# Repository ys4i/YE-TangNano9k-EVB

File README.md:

# YE-TangNano9k-EValuationBoard

コミックマーケット(C106)同人誌用TangNano9kの開発ボードです  
某月電子通商 Bタイプ基板(95×72mm)と寸法に互換性があります  
`販売コード[110243] B基板用アクリルパネル(アクリル板) 2mm厚(透明)`  
などでパネルを作れます

Tang Nano 9Kを用いた評価用ボードです。KiCad 9.0.3で設計されており、コミックマーケット(C106)頒布向けに作成されました。

## 特長
- 基板サイズ: 95 mm × 72 mm。某月電子通商 Bタイプ基板と同寸で、市販のB基板用アクリルパネルが使用可能。
- Seeed Studio製Tang Nano 9Kモジュールを搭載 (U1)。
- 24ピン×2列の拡張用ソケットコネクタを左右に配置 (J1, J2)。
- 4桁7セグメントLED表示器 OSL40391-IRA を搭載し、簡単な数値表示が可能。
- ブザー UGCM1205XP と、駆動用NPNトランジスタ 2SC1815 (Q1) を装備。
- 入力インターフェースとして SPDTスイッチ (SW1) とタクトスイッチ2個 (SW2, SW3) を搭載。

## プロジェクト構成
- `YE-tangnano9k-EVB.kicad_pro` : プロジェクト設定ファイル
- `YE-tangnano9k-EVB.kicad_sch` : 回路図
- `YE-tangnano9k-EVB.kicad_pcb` : 基板レイアウト
- `docs/YE-tangnano9k-EVB.pdf` : 回路図・基板図の閲覧用PDF
- `sym-lib-table` : シンボルライブラリ設定

## 使い方
KiCad 9.0以降で `.kicad_pro` ファイルを開き、回路図や基板データを編集してください。ファイル形式の詳細は [KiCad File Formats Documentation](https://dev-docs.kicad.org/en/file-formats/index.html) を参照してください。

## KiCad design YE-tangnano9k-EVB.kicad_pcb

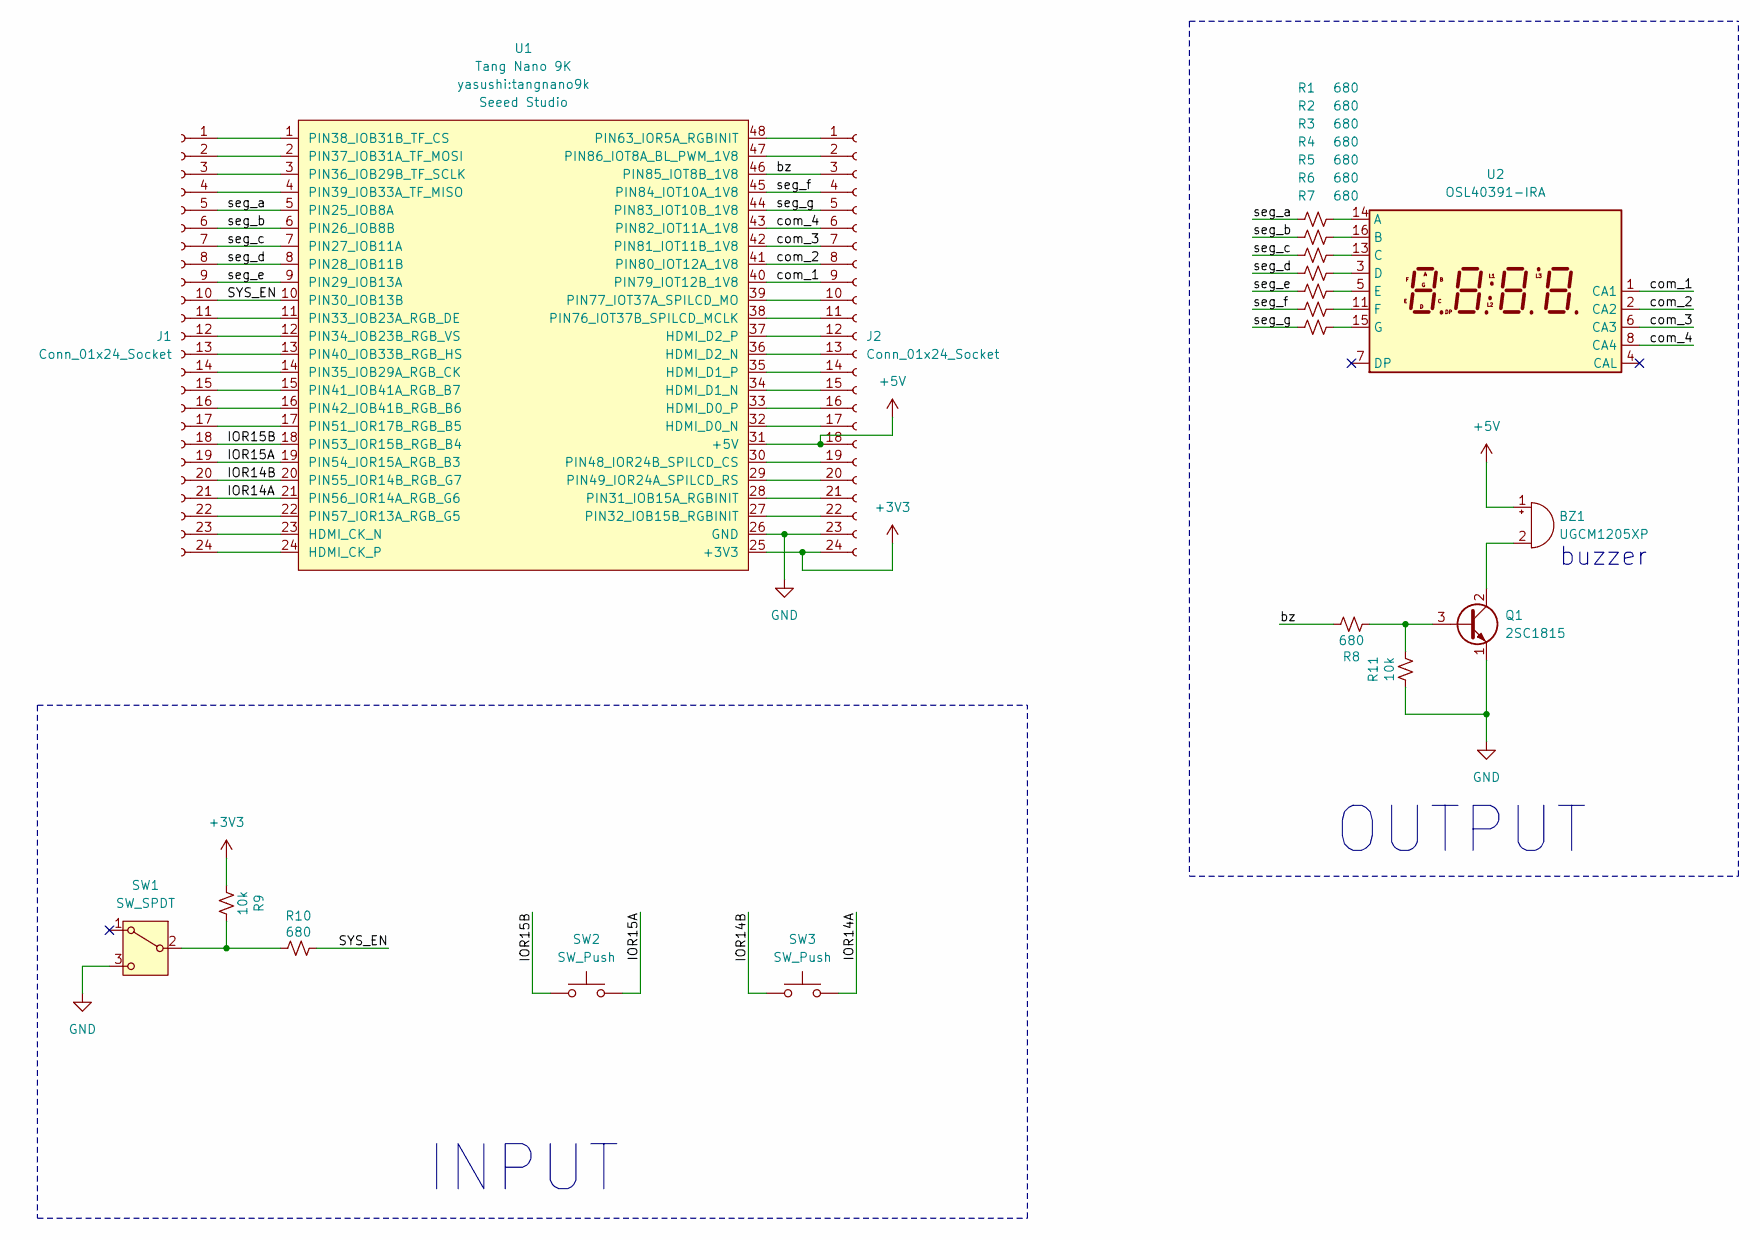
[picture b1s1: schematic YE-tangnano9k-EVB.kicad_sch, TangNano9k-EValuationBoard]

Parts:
BZ1: UGCM1205XP; Buzzer_12x9.5RM7.6
J1, J2: Conn_01x24_Socket; PinSocket_1x24_P2.54mm_Vertical
Q1: 2SC1815; TO-92_Inline_Wide
R1, R2, R3, R4, R5, R6, R7, R8, R10: 680; R_Axial_DIN0207_L6.3mm_D2.5mm_P10.16mm_Horizontal
R9, R11: 10k; R_Axial_DIN0207_L6.3mm_D2.5mm_P10.16mm_Horizontal
SW1: SW_SPDT; 2MS1-T1-B4-VS2-Q-E-S
SW2, SW3: SW_Push; SW_PUSH_6mm_H7.3mm
U1: Tang Nano 9K; tangnano9k
U2: OSL40391-IRA; OSL40391-Ixx

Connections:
+3V3: J2.24, R9.1, U1.25 (+3V3)
+5V: BZ1.1 (+), J2.18, U1.31 (+5V)
/IOR14A: J1.21, SW3.2, U1.21 (PIN56_IOR14A_RGB_G6)
/IOR14B: J1.20, SW3.1, U1.20 (PIN55_IOR14B_RGB_G7)
/IOR15A: J1.19, SW2.2, U1.19 (PIN54_IOR15A_RGB_B3)
/IOR15B: J1.18, SW2.1, U1.18 (PIN53_IOR15B_RGB_B4)
/SYS_EN: J1.10, R10.2, U1.10 (PIN30_IOB13B)
/bz: J2.3, R8.2, U1.46 (PIN85_IOT8B_1V8)
/com_1: J2.9, U1.40 (PIN79_IOT12B_1V8), U2.1 (CA1)
/com_2: J2.8, U1.41 (PIN80_IOT12A_1V8), U2.2 (CA2)
/com_3: J2.7, U1.42 (PIN81_IOT11B_1V8), U2.6 (CA3)
/com_4: J2.6, U1.43 (PIN82_IOT11A_1V8), U2.8 (CA4)
/seg_a: J1.5, R1.1, U1.5 (PIN25_IOB8A)
/seg_b: J1.6, R2.1, U1.6 (PIN26_IOB8B)
/seg_c: J1.7, R3.1, U1.7 (PIN27_IOB11A)
/seg_d: J1.8, R4.1, U1.8 (PIN28_IOB11B)
/seg_e: J1.9, R5.1, U1.9 (PIN29_IOB13A)
/seg_f: J2.4, R6.1, U1.45 (PIN84_IOT10A_1V8)
/seg_g: J2.5, R7.1, U1.44 (PIN83_IOT10B_1V8)
GND: J2.23, Q1.1 (E), R11.1, SW1.3 (C), U1.26 (GND)
unnamed: BZ1.2 (-), Q1.2 (C)
unnamed: J1.1, U1.1 (PIN38_IOB31B_TF_CS)
unnamed: J1.2, U1.2 (PIN37_IOB31A_TF_MOSI)
unnamed: J1.3, U1.3 (PIN36_IOB29B_TF_SCLK)
unnamed: J1.4, U1.4 (PIN39_IOB33A_TF_MISO)
unnamed: J1.11, U1.11 (PIN33_IOB23A_RGB_DE)
unnamed: J1.12, U1.12 (PIN34_IOB23B_RGB_VS)
unnamed: J1.13, U1.13 (PIN40_IOB33B_RGB_HS)
unnamed: J1.14, U1.14 (PIN35_IOB29A_RGB_CK)
unnamed: J1.15, U1.15 (PIN41_IOB41A_RGB_B7)
unnamed: J1.16, U1.16 (PIN42_IOB41B_RGB_B6)
unnamed: J1.17, U1.17 (PIN51_IOR17B_RGB_B5)
unnamed: J1.22, U1.22 (PIN57_IOR13A_RGB_G5)
unnamed: J1.23, U1.23 (HDMI_CK_N)
unnamed: J1.24, U1.24 (HDMI_CK_P)
unnamed: J2.1, U1.48 (PIN63_IOR5A_RGBINIT)
unnamed: J2.2, U1.47 (PIN86_IOT8A_BL_PWM_1V8)
unnamed: J2.10, U1.39 (PIN77_IOT37A_SPILCD_MO)
unnamed: J2.11, U1.38 (PIN76_IOT37B_SPILCD_MCLK)
unnamed: J2.12, U1.37 (HDMI_D2_P)
unnamed: J2.13, U1.36 (HDMI_D2_N)
unnamed: J2.14, U1.35 (HDMI_D1_P)
unnamed: J2.15, U1.34 (HDMI_D1_N)
unnamed: J2.16, U1.33 (HDMI_D0_P)
unnamed: J2.17, U1.32 (HDMI_D0_N)
unnamed: J2.19, U1.30 (PIN48_IOR24B_SPILCD_CS)
unnamed: J2.20, U1.29 (PIN49_IOR24A_SPILCD_RS)
unnamed: J2.21, U1.28 (PIN31_IOB15A_RGBINIT)
unnamed: J2.22, U1.27 (PIN32_IOB15B_RGBINIT)
unnamed: Q1.3 (B), R8.1, R11.2
unnamed: R9.2, R10.1, SW1.2 (B)
unnamed: R1.2, U2.14 (A)
unnamed: R2.2, U2.16 (B)
unnamed: R3.2, U2.13 (C)
unnamed: R4.2, U2.3 (D)
unnamed: R5.2, U2.5 (E)
unnamed: R6.2, U2.11 (F)
unnamed: R7.2, U2.15 (G)

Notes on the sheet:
OUTPUT
INPUT
buzzer

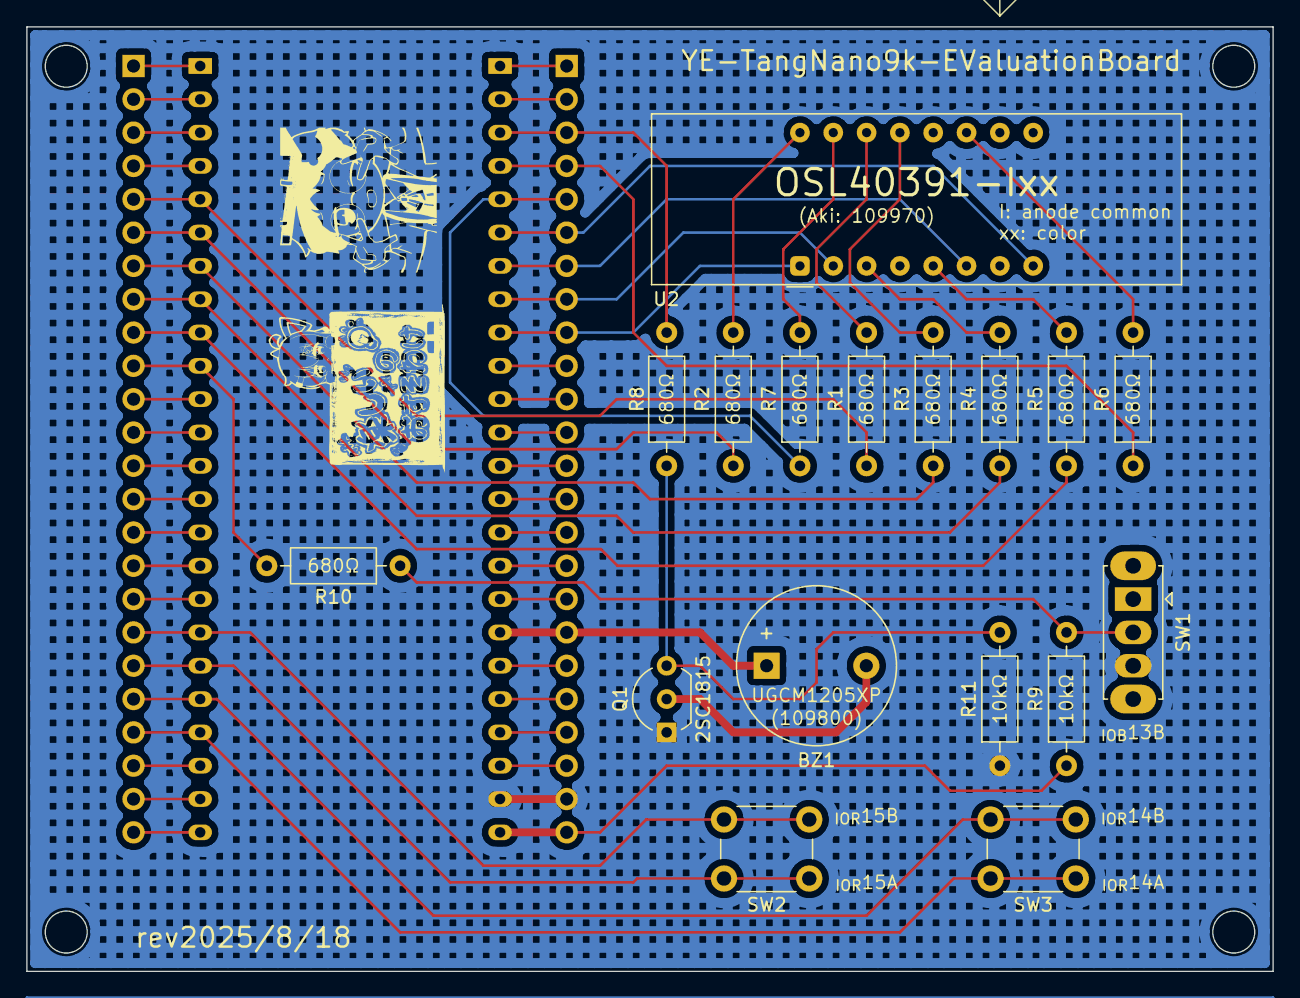
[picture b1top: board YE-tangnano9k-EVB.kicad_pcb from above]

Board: 2 copper layers, 95.0 x 72.0 mm, 20 parts (0 on the bottom side), 58 nets.

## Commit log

2025-08-04 first
2025-08-04 add yasushi_icon fix Front_silk
2025-08-04 fix net_name
2025-08-05 change pushSW net change buzzer logic(ActiveHigh → ActiveLow)
2025-08-06 change Buzzer_logic (→ActiveHIGH) fix pcb
2025-08-06 fix silk font size
2025-08-06 add silk art
2025-08-06 塗りつぶしをmeshに変更
2025-08-06 meshのみを下に置いとく
2025-08-06 fix BottomMask Layer
2025-08-08 fix date
2025-08-08 Insert original project description
2025-08-17 fix silk(buzzer)
2025-08-17 fix revision date
2026-03-25 add schematic gitignore
2026-03-25 Add .gitignore for local KiCad artifacts and backups
2026-03-25 README: docs内PDFへの案内を追加
